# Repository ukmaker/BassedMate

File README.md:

# BassedMate
A drum machine using the Teensy 4.1 and VS1053 MIDI chip

It's dead sir. Look for the BassMate project instead. They is even spelt diffrnt innit.

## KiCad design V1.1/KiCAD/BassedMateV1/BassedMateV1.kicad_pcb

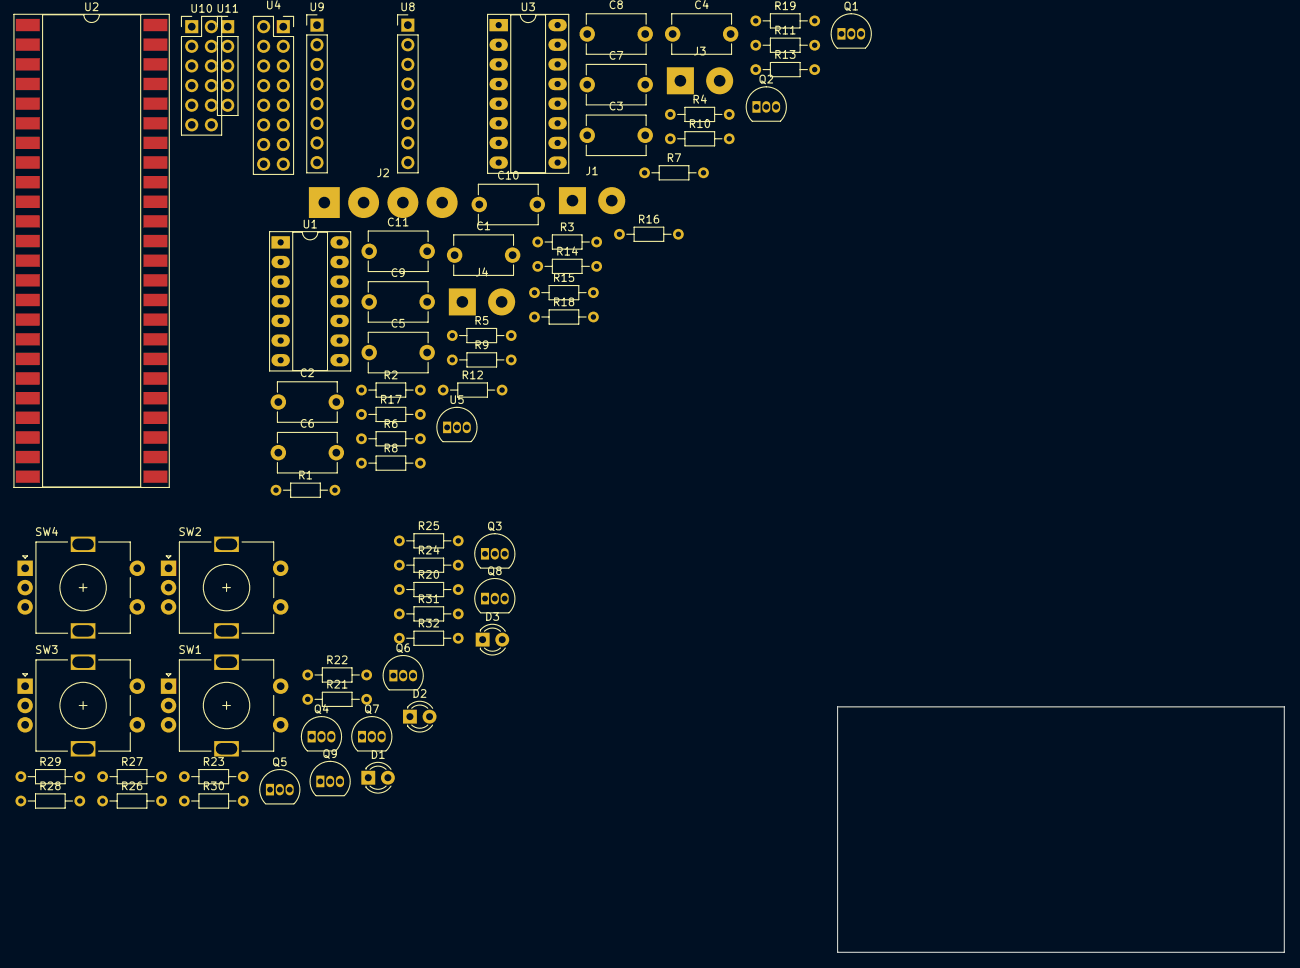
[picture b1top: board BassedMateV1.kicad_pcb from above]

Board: 2 copper layers, 57.8 x 31.8 mm, 72 parts (0 on the bottom side), 87 nets, no tracks yet.

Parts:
C1, C3, C4, C5, C6, C7, C8, C9, C10, C11: C; C_Disc_D7.5mm_W5.0mm_P7.50mm
C2: CP; C_Disc_D7.5mm_W5.0mm_P7.50mm
D1, D2, D3: RED LED; LED_D3.0mm
J1: Conn_Coaxial; SolderWirePad_1x02_P5.08mm_Drill1.5mm
J2: AudioJack3_Switch; SolderWirePad_1x04_P5.08mm_Drill1.5mm
J3, J4: Screw_Terminal_01x02; SolderWirePad_1x02_P5.08mm_Drill1.5mm
Q1: Q_NJFET_DGS; TO-92_Inline
Q2: Q_NPN_CBE; TO-92_Inline
Q3, Q4, Q5, Q6: ZTX313; TO-92_Inline
Q7, Q8, Q9: ZTX213; TO-92_Inline
R1, R2, R3, R4, R5, R6, R7, R8, R9, R10, R11, R12, R13, R14, R15, R16, R17, R18, R19: R; R_Axial_DIN0204_L3.6mm_D1.6mm_P7.62mm_Horizontal
R20, R21, R22, R23, R26, R29, R32: 1K; R_Axial_DIN0204_L3.6mm_D1.6mm_P7.62mm_Horizontal
R24: 120R; R_Axial_DIN0204_L3.6mm_D1.6mm_P7.62mm_Horizontal
R25, R28, R31: 15K; R_Axial_DIN0204_L3.6mm_D1.6mm_P7.62mm_Horizontal
R27, R30: 56R; R_Axial_DIN0204_L3.6mm_D1.6mm_P7.62mm_Horizontal
SW1, SW2, SW3, SW4: Rotary_Encoder_Switch; RotaryEncoder_Alps_EC11E-Switch_Vertical_H20mm
U1: MC33179; DIP-14_W7.62mm_Socket_LongPads
U2: Teensy4.1; DIP-48_W16.51mm_SMDSocket_LongPads
U3: AD5204; DIP-16_W7.62mm_Socket_LongPads
U4: VS1053_Module; PinSocket_2x08_P2.54mm_Vertical
U5: LE33_TO92; TO-92_Inline
U8: PAM8403_Module; PinHeader_1x08_P2.54mm_Vertical
U9: TFT_LCD_SPI_160X128; PinHeader_1x08_P2.54mm_Vertical
U10: ButtonPad_2x2; PinHeader_2x06_P2.54mm_Vertical
U11: Adafruit_NeoTrellis_4X8; PinHeader_1x05_P2.54mm_Vertical

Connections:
+3.3VA: C1.1, C9.2, Q1.1, R1.1, R9.2, U1.4, U5.1
+3V3: C7.1, U2.46, U3.5, U3.6, U3.7, U9.2, U9.8, U11.4
+5V: C8.2, R24.1, R25.1, R27.1, R28.1, R30.1, R31.1, U2.48, U4.1, U4.2, U5.3, U8.1
BE_B: SW3.S1, U2.31
BE_L: SW3.A, U2.33
BE_R: SW3.B, U2.32
DP_CLK: U2.38, U3.9
DP_CS: U2.37, U3.4
DP_SDI: U2.39, U3.8
FE_B: SW4.S1, U2.43
FE_L: SW4.A, U2.45
FE_R: SW4.B, U2.44
GND: C1.2, C2.2, C4.2, C5.2, C7.2, C8.1, C9.1, J1.2, Q2.3, Q3.3, Q4.3, Q5.3, Q6.3, R2.2, R4.2, R5.2, R10.1, SW1.C, SW1.S2, SW2.C, SW2.S2, SW3.C, SW3.S2, SW4.C, SW4.S2, U1.11, U2.1, U2.34, U2.47, U3.11, U4.3, U4.14, U5.2, U8.2, U8.4, U9.1, U10.8, U11.3
HPHONE: Q2.1, R9.1, U2.10
MP_CS: U2.17, U4.9
MP_DCS: U2.12, U4.10
MP_MISO: U2.14, U4.4
MP_MOSI: U2.13, U4.5
MP_RESET: U2.16, U4.8
MP_SCK: U2.35, U4.6
NT_INT: U2.40, U11.5
NT_SCL: U2.42, U11.2
NT_SDA: U2.41, U11.1
unnamed: C2.1, C4.1, R1.2, R2.1, U1.3
unnamed: C3.1, R3.2
unnamed: C3.2, J1.1
unnamed: C5.1, Q1.2, R3.1, R4.1
unnamed: C6.1, R6.1, U1.5
unnamed: C6.2, Q1.3, R5.1
unnamed: C10.2, R18.1, U1.8
unnamed: C11.2, R19.1, U1.14
unnamed: D1.1, R26.2
unnamed: D1.2, Q7.1, R25.2
unnamed: D2.1, R29.2
unnamed: D2.2, Q8.1, R28.2
unnamed: D3.1, R32.2
unnamed: D3.2, Q9.1, R31.2
unnamed: R15.2, U4.13
unnamed: R13.2, R14.2, U4.12
unnamed: R12.2, U4.11
unnamed: J3.1, U8.6
unnamed: J3.2, U8.7
unnamed: J4.1, U8.8
unnamed: Q2.2, R10.2, R11.1
unnamed: Q3.1, R20.2
unnamed: Q3.2, U10.4
unnamed: Q4.1, R21.2
unnamed: Q4.2, U10.5
unnamed: Q5.1, R22.2
unnamed: Q5.2, U10.6
unnamed: Q6.1, R23.2
unnamed: Q6.2, U10.7
unnamed: Q7.2, U10.1
unnamed: Q7.3, R24.2
unnamed: Q8.2, U10.2
unnamed: Q8.3, R27.2
unnamed: Q9.2, U10.3
unnamed: Q9.3, R30.2
unnamed: R7.1, R8.2, U1.6
unnamed: R8.1, U1.7, U3.16
unnamed: R12.1, R18.2, U1.9
unnamed: R13.1, R16.2, U1.10
unnamed: R14.1, R17.1, U1.12
unnamed: R15.1, R19.2, U1.13
SC_CS: U2.2, U9.7
SC_DC: U2.20, U9.6
SC_RESET: U2.21, U9.5
SC_SCL: U2.19, U9.3
SC_SDA: U2.18, U9.4
TE_B: SW2.S1, U2.36
TE_L: SW2.A, U2.30
TE_R: SW2.B, U2.29
TR_B: R32.1, U2.5
TR_B1: U2.25, U10.12
TR_B2: U2.26, U10.11
TR_B3: U2.27, U10.10
TR_B4: U2.28, U10.9
TR_G: R29.1, U2.4
TR_LG1: R20.1, U2.6
TR_LG2: R21.1, U2.7
TR_LG3: R22.1, U2.8
TR_LG4: R23.1, U2.9
TR_R: R26.1, U2.3
VE_B: SW1.S1, U2.24
VE_L: SW1.A, U2.22
VE_R: SW1.B, U2.23
VREF: R6.2, R7.2, R16.1, R17.2, U1.1, U1.2

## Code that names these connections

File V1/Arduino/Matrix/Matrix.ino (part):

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/**
 * Screen is an ST7735 based 1.8" screen without touch
 */
#define SC_SCL 27
#define SC_SDA 26
#define SC_CS 0
#define SC_DC 28
#define SC_RESET 29

/**
 * Music player is a VS1053 basic breakout board
 */
#define MP_MOSI 11
#define MP_MISO 12
#define MP_SCK 13
#define MP_CS 25
#define MP_DCS 10
#define MP_DREQ UNUSED
#define MP_RESET 24

#define ENC_VOL_L 30
#define ENC_VOL_R 31
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#define ENC_TONE_R 37 
#define ENC_TONE_B 14

#define DP_CS 15
#define DP_CLK 16
#define DP_SDI 17
#define DP_MASTER_VOL 2

// The 2x2 Keypad
#define TR_R 1
#define TR_G 2
#define TR_B 3
#define TR_LG1 4
#define TR_LG2 5
#define TR_LG3 6
#define TR_LG4 7
#define TR_B1 33
#define TR_B2 34
#define TR_B3 35
#define TR_B4 36

#define VOICE_BUTTON 2
#define VELOCITY_BUTTON 3
#define RUN_STOP_BUTTON 0
#define EFFECTS_BUTTON 1

#define RUNSTOP_STOPPED_COLOUR TR_R
#define RUNSTOP_PAUSED_COLOUR (TR_R + TR_G)
#define RUNSTOP_RUNNING_COLOUR TR_G

ST7735_t3 tft = ST7735_t3(SC_CS, SC_DC, SC_SDA, SC_SCL, SC_RESET);

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
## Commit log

2021-05-31 initial import
2021-06-02 Added long press support to the grid and 2x2
2022-04-06 Big batch of updates. V1.1 contains the latest working code for the Teensy platform
2022-04-06 deleted file

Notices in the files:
V1/Arduino/Matrix/Matrix.ino:
Copyright 2021 Duncan McIntyre
